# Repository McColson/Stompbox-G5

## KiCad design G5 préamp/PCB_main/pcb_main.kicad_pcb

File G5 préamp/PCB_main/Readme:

Kicad Project files for the main PCB
pcb_main.png

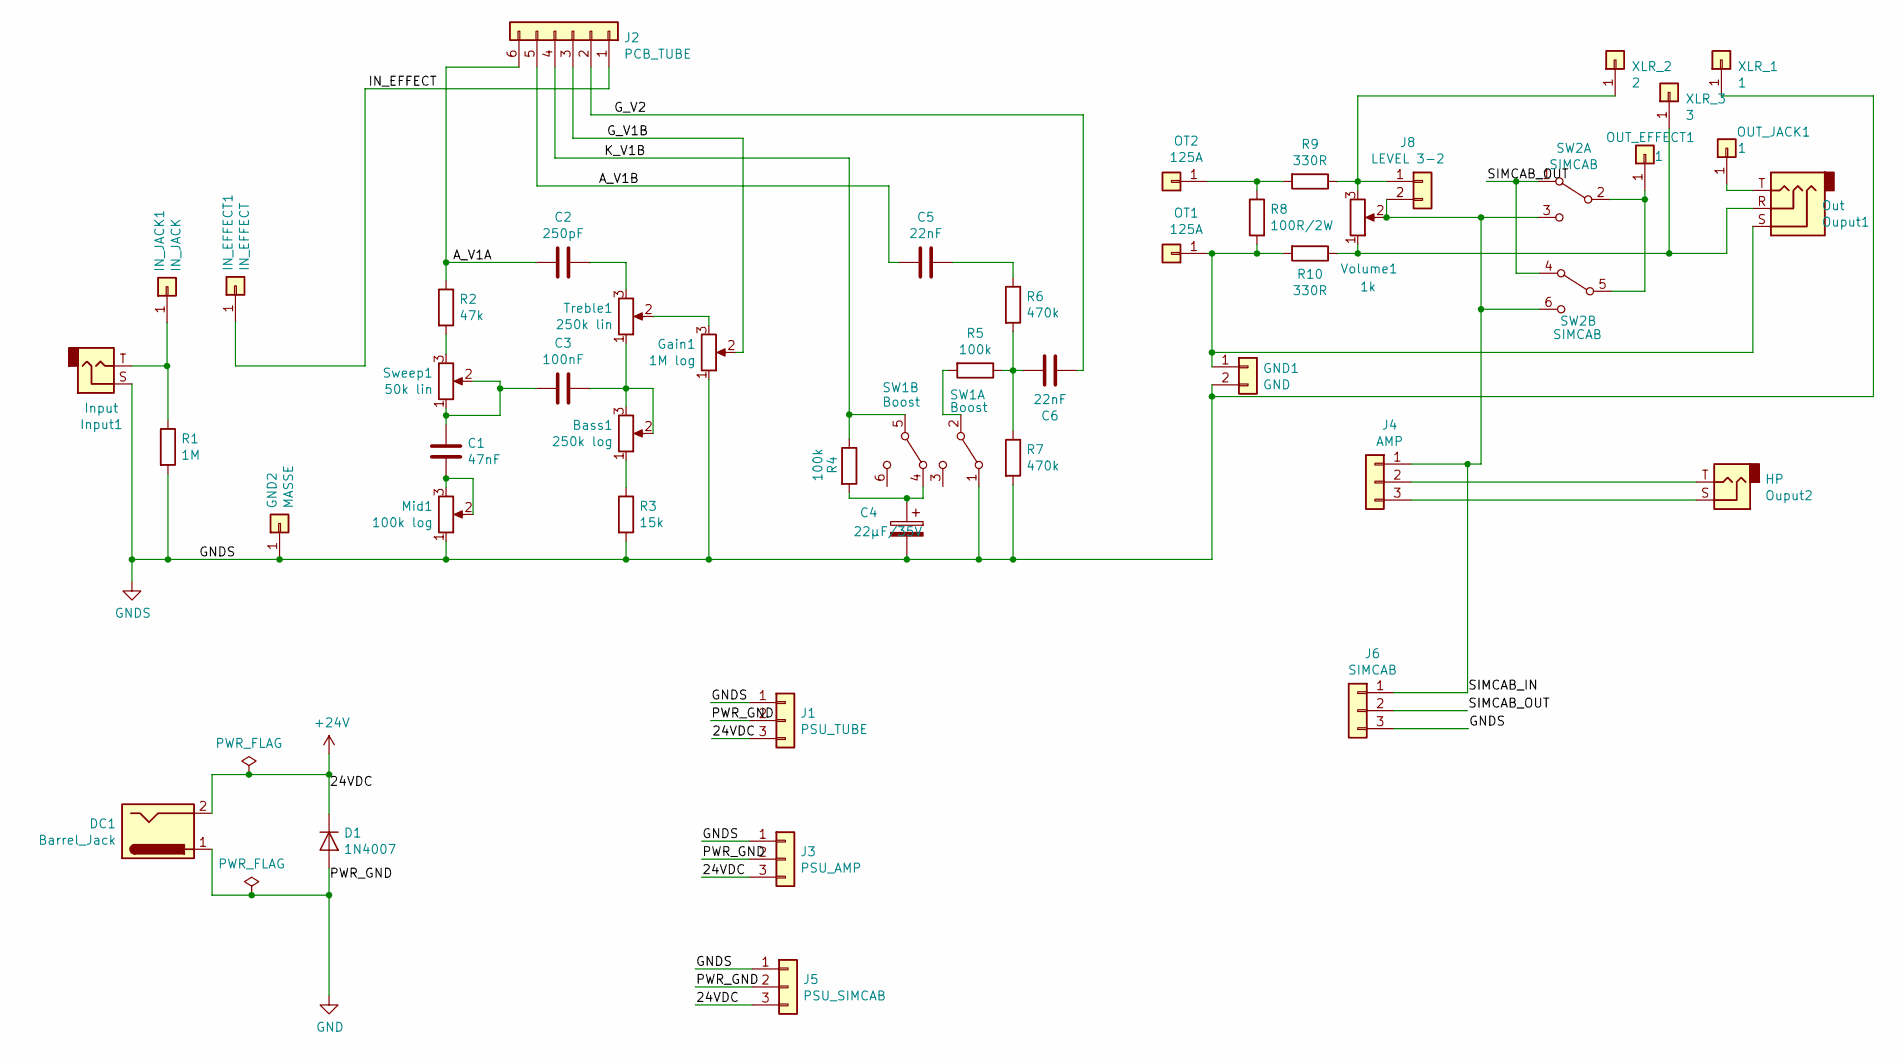
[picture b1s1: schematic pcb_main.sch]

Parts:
Bass1: 250k log; Potentiometer_Omeg_PC16BU_Vertical
C1: 47nF; C_Rect_L7.2mm_W3.0mm_P5.00mm_FKS2_FKP2_MKS2_MKP2
C2: 250pF; C_Disc_D7.5mm_W5.0mm_P7.50mm
C3: 100nF; C_Rect_L7.2mm_W3.0mm_P5.00mm_FKS2_FKP2_MKS2_MKP2
C4: 22µF/35V; CP_Radial_D6.3mm_P2.50mm
C5, C6: 22nF; C_Rect_L7.2mm_W3.0mm_P5.00mm_FKS2_FKP2_MKS2_MKP2
D1: 1N4007; D_DO-41_SOD81_P7.62mm_Horizontal
DC1: Barrel_Jack; BarrelJack_Horizontal
GND1: GND; SolderWirePad_1x02_P7.62mm_Drill2mm
GND2: MASSE; SolderWirePad_1x01_Drill2mm
Gain1: 1M log; Potentiometer_Omeg_PC16BU_Vertical
IN_EFFECT1: IN_EFFECT; SolderWirePad_1x01_Drill2mm
IN_JACK1: IN_JACK; SolderWirePad_1x01_Drill2mm
Input1: Input; Jack_3.5mm_Neutrik_NMJ6HCD2_Horizontal
J1: PSU_TUBE; PinHeader_1x03_P2.54mm_Horizontal
J2: PCB_TUBE; PinHeader_1x06_P2.54mm_Horizontal
J3: PSU_AMP; PinHeader_1x03_P2.54mm_Horizontal
J4: AMP; PinHeader_1x03_P2.54mm_Horizontal
J5: PSU_SIMCAB; PinHeader_1x03_P2.54mm_Horizontal
J6: SIMCAB; PinHeader_1x03_P2.54mm_Horizontal
J8: LEVEL 3-2; SolderJumper-2_P1.3mm_Open_Pad1.0x1.5mm
Mid1: 100k log; Potentiometer_Omeg_PC16BU_Vertical
OT1, OT2: 125A; SolderWirePad_1x01_Drill2mm
OUT_EFFECT1: 1; SolderWirePad_1x01_Drill2mm
OUT_JACK1: 1; SolderWirePad_1x01_Drill2mm
Ouput1: Out; Jack_3.5mm_Neutrik_NMJ6HCD2_Horizontal
Ouput2: HP; Jack_3.5mm_Neutrik_NMJ6HCD2_Horizontal
R1: 1M; R_Axial_DIN0207_L6.3mm_D2.5mm_P7.62mm_Horizontal
R2: 47k; R_Axial_DIN0207_L6.3mm_D2.5mm_P7.62mm_Horizontal
R3: 15k; R_Axial_DIN0207_L6.3mm_D2.5mm_P7.62mm_Horizontal
R4, R5: 100k; R_Axial_DIN0207_L6.3mm_D2.5mm_P7.62mm_Horizontal
R6, R7: 470k; R_Axial_DIN0207_L6.3mm_D2.5mm_P7.62mm_Horizontal
R8: 100R/2W; R_Axial_DIN0207_L6.3mm_D2.5mm_P10.16mm_Horizontal
R9, R10: 330R; R_Axial_DIN0207_L6.3mm_D2.5mm_P7.62mm_Horizontal
SW1: Boost; SW_CK_Lever_DPDT_72xx
SW2: SIMCAB; SW_CK_Lever_DPDT_72xx
Sweep1: 50k lin; Potentiometer_Omeg_PC16BU_Vertical
Treble1: 250k lin; Potentiometer_Omeg_PC16BU_Vertical
Volume1: 1k; Potentiometer_Omeg_PC16BU_Vertical
XLR_1: 1; SolderWirePad_1x01_Drill2mm
XLR_2: 2; SolderWirePad_1x01_Drill2mm
XLR_3: 3; SolderWirePad_1x01_Drill2mm

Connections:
+24V: D1.1 (K), DC1.2, J1.3, J3.3, J5.3
/A_V1A: C2.2, J2.6, R2.1
/A_V1B: C5.2, J2.5
/G_V1B: Gain1.2, J2.3
/G_V2: C6.1, J2.2
/IN_EFFECT: IN_EFFECT1.1, J2.1
/K_V1B: J2.4, R4.1, SW1.5 (B)
/SIMCAB_IN: J4.1, J6.1, J8.2, SW2.3 (C), SW2.6 (C), Volume1.2
/SIMCAB_OUT: J6.2, SW2.1 (A), SW2.4 (A)
GND: D1.2 (A), DC1.1, J1.2, J3.2, J5.2
GNDS: C4.2, GND1.2, GND2.1, Gain1.1, Input1.S, J1.1, J3.1, J5.1, J6.3, Mid1.1, R1.2, R3.2, R7.2, SW1.1 (A), XLR_1.1
unnamed: Bass1.1, R3.1
unnamed: Bass1.2, Bass1.3, C3.1, Treble1.1
unnamed: C1.1, C3.2, Sweep1.1, Sweep1.2
unnamed: C1.2, Mid1.2, Mid1.3
unnamed: C2.1, Treble1.3
unnamed: C4.1, R4.2, SW1.4 (A)
unnamed: C5.1, R6.1
unnamed: C6.2, R5.1, R6.2, R7.1
unnamed: GND1.1, OT1.1, Ouput1.S, R8.2, R10.2
unnamed: Gain1.3, Treble1.2
unnamed: IN_JACK1.1, Input1.T, R1.1
unnamed: J4.2, Ouput2.T
unnamed: J4.3, Ouput2.S
unnamed: J8.1, R9.1, Volume1.3, XLR_2.1
unnamed: OT2.1, R8.1, R9.2
unnamed: OUT_EFFECT1.1, SW2.2 (B), SW2.5 (B)
unnamed: OUT_JACK1.1, Ouput1.T
unnamed: Ouput1.R, R10.1, Volume1.1, XLR_3.1
unnamed: R2.2, Sweep1.3
unnamed: R5.2, SW1.2 (B)

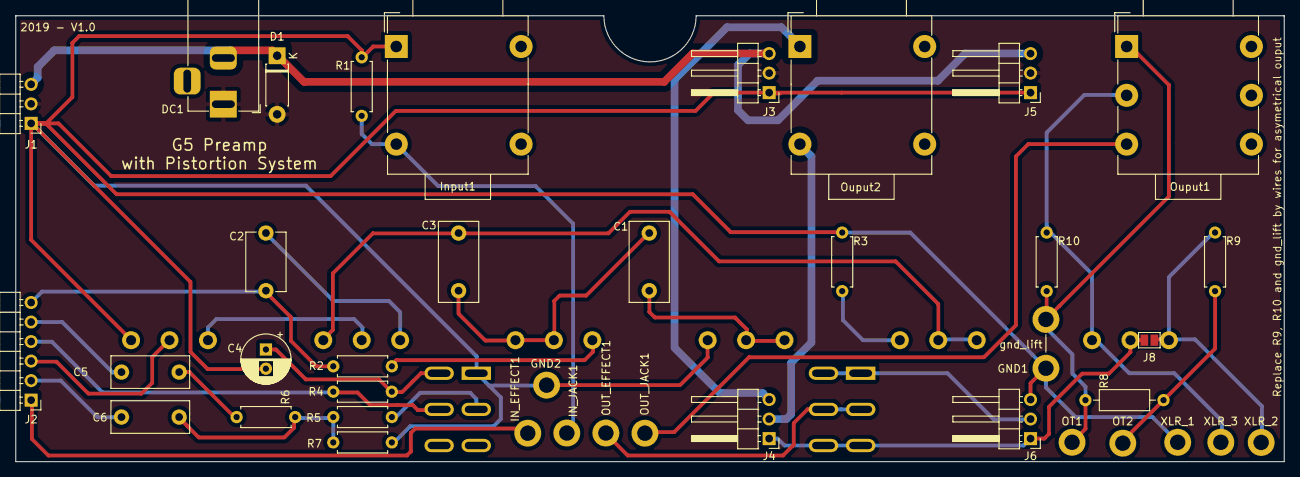
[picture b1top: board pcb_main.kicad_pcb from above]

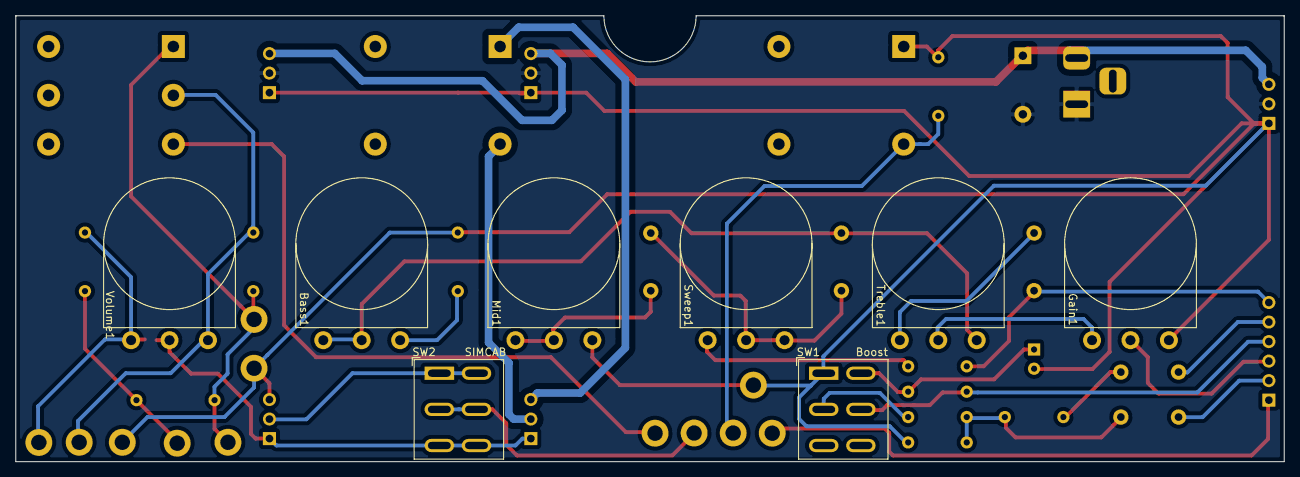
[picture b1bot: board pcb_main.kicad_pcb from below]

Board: 2 copper layers, 165.0 x 58.0 mm, 47 parts (8 on the bottom side), 31 nets.

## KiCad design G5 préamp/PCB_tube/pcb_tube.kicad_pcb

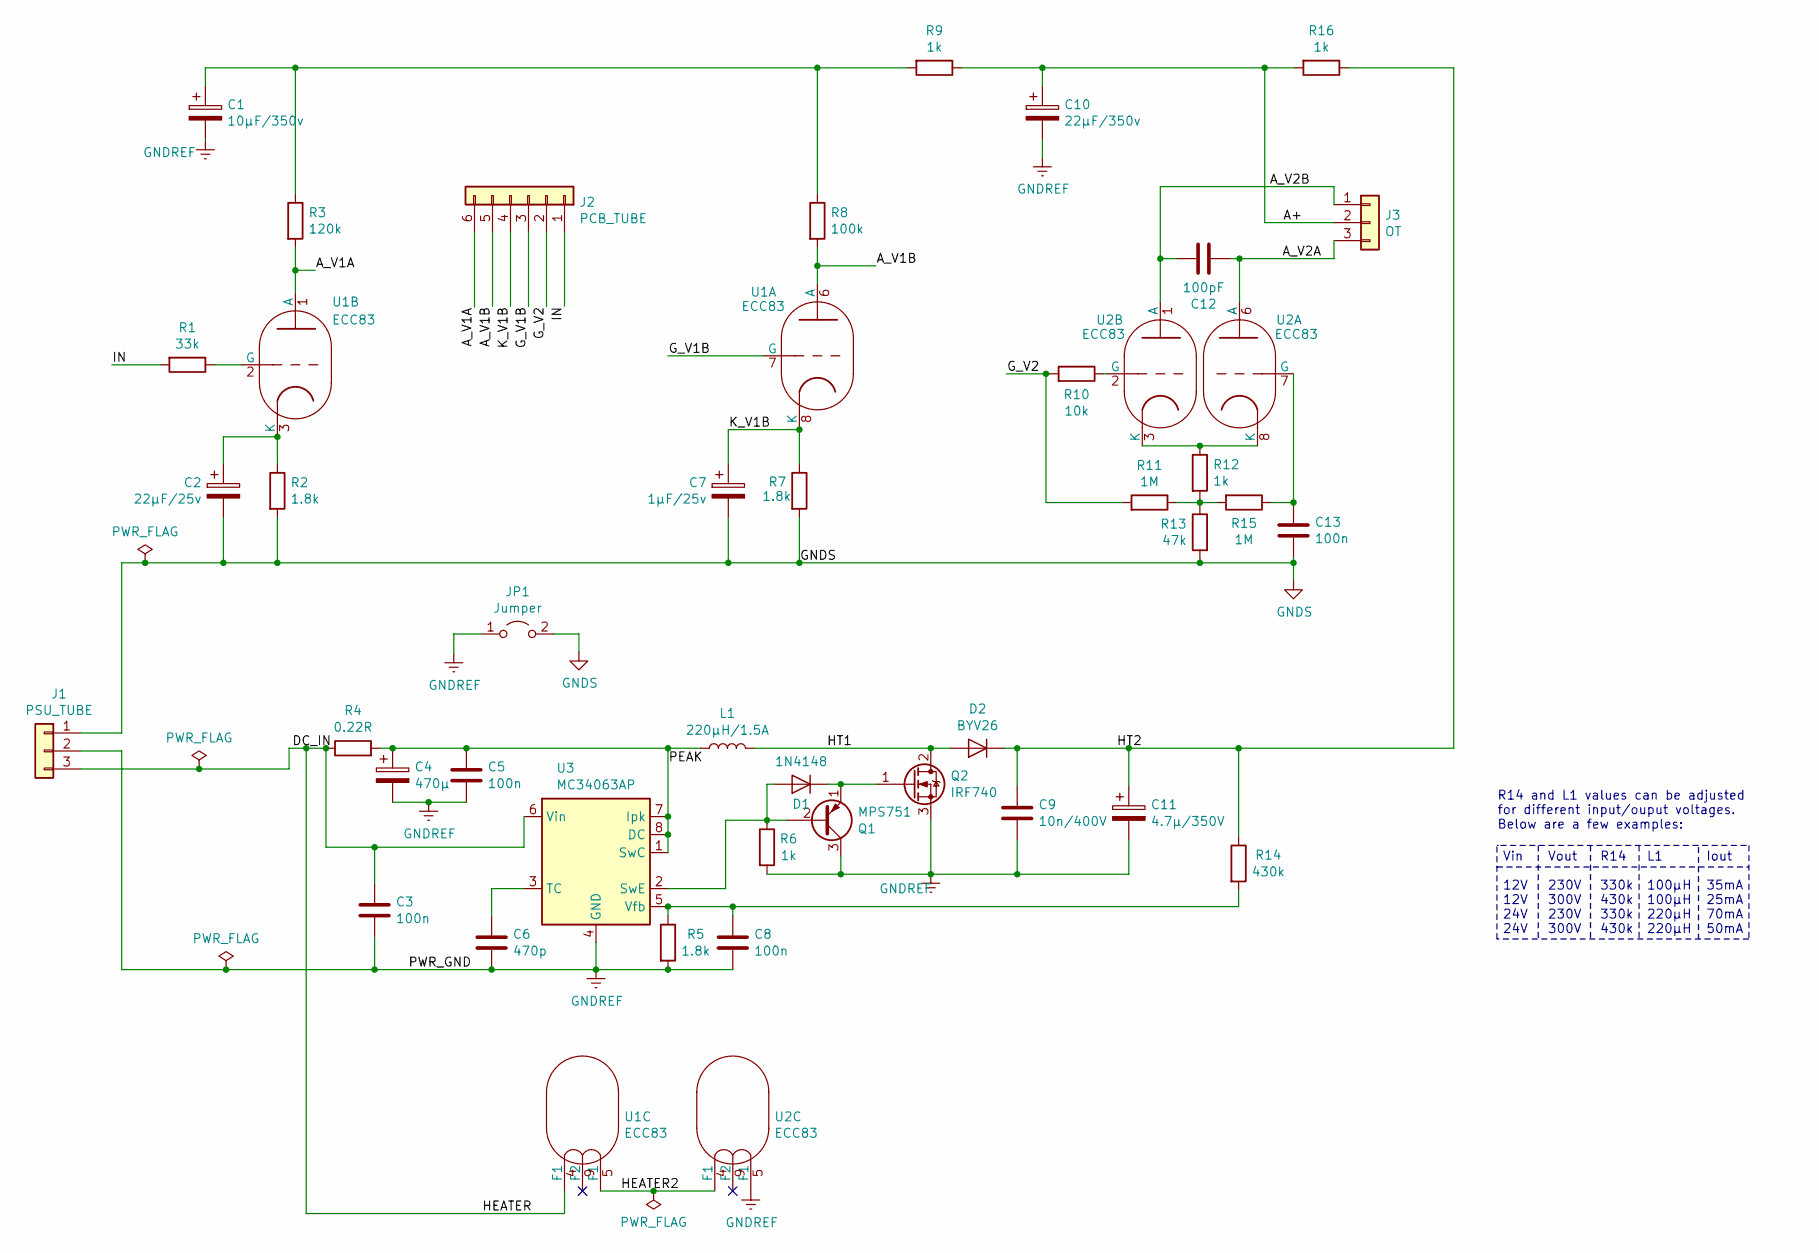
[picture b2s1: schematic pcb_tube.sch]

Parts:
C1: 10µF/350v; CP_Radial_D10.0mm_P5.00mm
C2: 22µF/25v; CP_Radial_D6.3mm_P2.50mm
C3, C5, C8: 100n; C_Rect_L7.2mm_W3.0mm_P5.00mm_FKS2_FKP2_MKS2_MKP2; MPN MKS2D031001A00KI00
C4: 470µ; CP_Radial_D10.0mm_P5.00mm; MPN UVR1V471MPD
C6: 470p; C_Disc_D6.0mm_W4.4mm_P5.00mm; MPN C322C471J2G5TA
C7: 1µF/25v; CP_Radial_D6.3mm_P2.50mm
C9: 10n/400V; C_Disc_D6.0mm_W4.4mm_P5.00mm; MPN C322C103KBR5TA
C10: 22µF/350v; CP_Radial_D13.0mm_P5.00mm
C11: 4.7µ/350V; CP_Radial_D10.0mm_P5.00mm; MPN UBT2V4R7MPD8
C12: 100pF; C_Disc_D7.5mm_W5.0mm_P7.50mm
C13: 100n; C_Rect_L7.2mm_W3.0mm_P5.00mm_FKS2_FKP2_MKS2_MKP2
D1: 1N4148; D_DO-35_SOD27_P7.62mm_Horizontal; MPN 1N4148TR
D2: BYV26; D_DO-15_P10.16mm_Horizontal; MPN BYV26E-TAP
J1: PSU_TUBE; PinSocket_1x03_P2.54mm_Vertical
J2: PCB_TUBE; PinSocket_1x06_P2.54mm_Vertical
J3: OT; TerminalBlock_bornier-3_P5.08mm
JP1: Jumper; SolderJumper-2_P1.3mm_Bridged_RoundedPad1.0x1.5mm
L1: 220µH/1.5A; L_Radial_D10.5mm_P5.00mm_MuRATA_1200RS; MPN 12RS104C
Q1: MPS751; TO-92_Inline_Wide; MPN MPS751G
Q2: IRF740; TO-220-3_Vertical; MPN IRF740LCPBF
R1: 33k; R_Axial_DIN0207_L6.3mm_D2.5mm_P7.62mm_Horizontal
R2, R7: 1.8k; R_Axial_DIN0207_L6.3mm_D2.5mm_P7.62mm_Horizontal
R3: 120k; R_Axial_DIN0207_L6.3mm_D2.5mm_P7.62mm_Horizontal
R4: 0.22R; R_Axial_DIN0207_L6.3mm_D2.5mm_P7.62mm_Horizontal; MPN LR1F220R
R5: 1.8k; R_Axial_DIN0207_L6.3mm_D2.5mm_P7.62mm_Horizontal; MPN LR1F1K8
R6: 1k; R_Axial_DIN0207_L6.3mm_D2.5mm_P7.62mm_Horizontal; MPN LR1F1K0
R8: 100k; R_Axial_DIN0207_L6.3mm_D2.5mm_P7.62mm_Horizontal
R9, R12, R16: 1k; R_Axial_DIN0207_L6.3mm_D2.5mm_P7.62mm_Horizontal
R10: 10k; R_Axial_DIN0207_L6.3mm_D2.5mm_P7.62mm_Horizontal
R11, R15: 1M; R_Axial_DIN0207_L6.3mm_D2.5mm_P7.62mm_Horizontal
R13: 47k; R_Axial_DIN0207_L6.3mm_D2.5mm_P7.62mm_Horizontal
R14: 430k; R_Axial_DIN0207_L6.3mm_D2.5mm_P7.62mm_Horizontal; MPN YR1B432KCC
U1, U2: ECC83; Valve_Noval-B9A_Belton-VT9-PT_Socket
U3: MC34063AP; DIP-8_W7.62mm_LongPads; MPN MC34063AP1G

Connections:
/A+: C10.1, R9.1, R16.2; also elsewhere on the board
/A_V1A: J2.6, R3.2, U1.1 (A)
/A_V1B: J2.5, R8.2, U1.6 (A)
/A_V2A: C12.1, U2.6 (A); also elsewhere on the board
/A_V2B: C12.2, U2.1 (A); also elsewhere on the board
/DC_IN: C3.1, J1.3, R4.1, U1.4 (F1), U3.6 (Vin)
/G_V1B: J2.3, U1.7 (G)
/G_V2: J2.2, R10.2, R11.2
/HEATER2: U1.5 (F1), U2.4 (F1)
/HT1: D2.2 (A), L1.2, Q2.2 (D)
/HT2: C9.1, C11.1, D2.1 (K), R14.1, R16.1
/IN: J2.1, R1.2
/K_V1B: C7.1, J2.4, R7.1, U1.8 (K)
/PEAK: C4.1, C5.1, L1.1, R4.2, U3.1 (SwC), U3.7 (Ipk), U3.8 (DC)
GNDREF: C1.2, C3.2, C4.2, C5.2, C6.2, C8.2, C9.2, C10.2, C11.2, J1.2, JP1.1 (A), Q1.3 (C), Q2.3 (S), R5.2, R6.2, U2.5 (F1), U3.4 (GND)
GNDS: C2.2, C7.2, C13.2, J1.1, JP1.2 (B), R2.2, R7.2, R13.2
unnamed: C1.1, R3.1, R8.1, R9.2
unnamed: C2.1, R2.1, U1.3 (K)
unnamed: C6.1, U3.3 (TC)
unnamed: C8.1, R5.1, R14.2, U3.5 (Vfb)
unnamed: C13.1, R15.1, U2.7 (G)
unnamed: D1.1 (K), Q1.1 (E), Q2.1 (G)
unnamed: D1.2 (A), Q1.2 (B), R6.1, U3.2 (SwE)
unnamed: R1.1, U1.2 (G)
unnamed: R10.1, U2.2 (G)
unnamed: R11.1, R12.2, R13.1, R15.2
unnamed: R12.1, U2.3 (K), U2.8 (K)

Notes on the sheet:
Vin 12V 12V 24V 24V
Vout 230V 300V 230V 300V
R14 330k 430k 330k 430k
L1 100µH 100µH 220µH 220µH
Iout 35mA 25mA 70mA 50mA
R14 and L1 values can be adjusted for different input/ouput voltages. Below are a few examples:

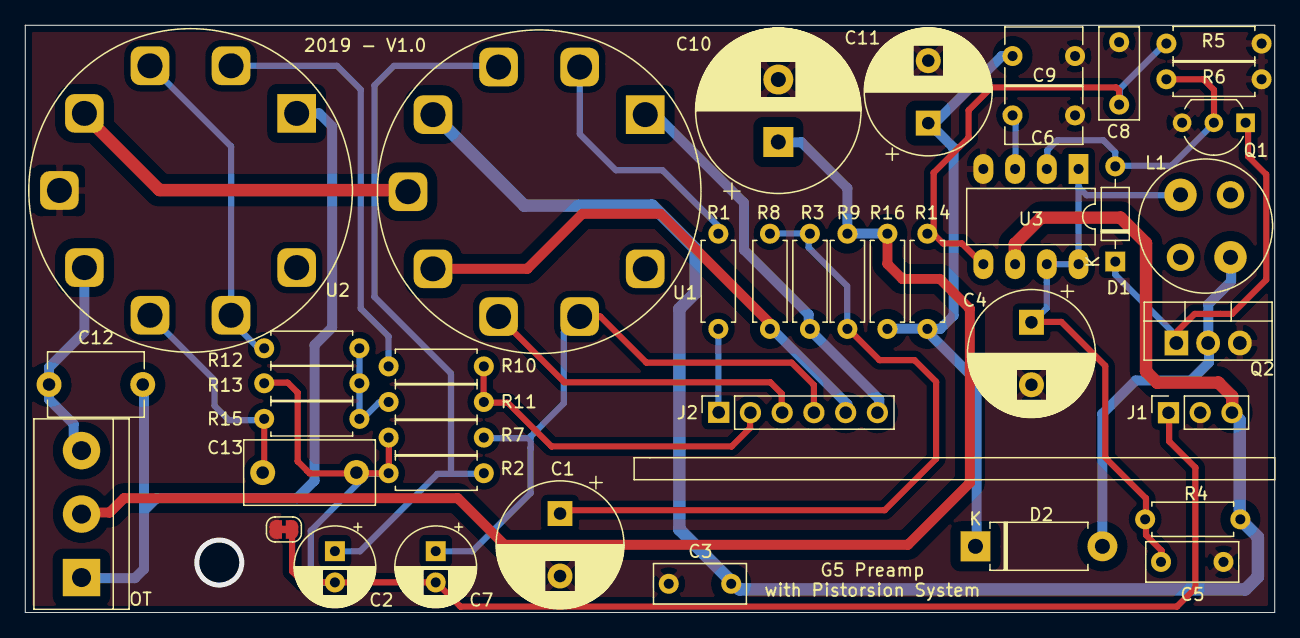
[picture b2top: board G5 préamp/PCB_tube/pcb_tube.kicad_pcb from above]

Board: 2 copper layers, 100.0 x 47.0 mm, 41 parts (0 on the bottom side), 27 nets.

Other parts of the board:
OT: OT; TerminalBlock_bornier-3_P5.08mm

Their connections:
/A+: OT.2; also elsewhere on the board
/A_V2A: OT.3; also elsewhere on the board
/A_V2B: OT.1; also elsewhere on the board

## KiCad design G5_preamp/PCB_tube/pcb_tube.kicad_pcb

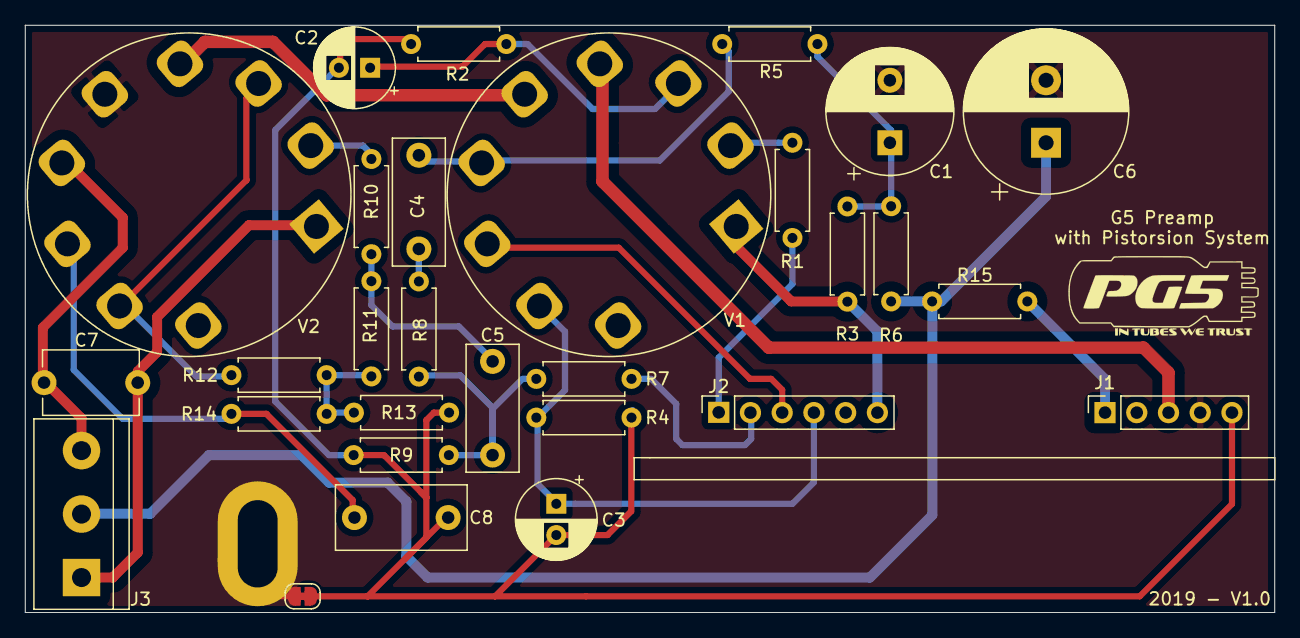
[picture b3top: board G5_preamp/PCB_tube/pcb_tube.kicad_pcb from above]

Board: 2 copper layers, 100.0 x 47.0 mm, 29 parts (0 on the bottom side), 24 nets.

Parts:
C1: 10µF/350v; CP_Radial_D10.0mm_P5.00mm
C2: 22µF/25v; CP_Radial_D6.3mm_P2.50mm
C3: 1µF/25v; CP_Radial_D6.3mm_P2.50mm
C4, C5: 22nF; C_Rect_L10.0mm_W4.0mm_P7.50mm_MKS4
C6: 22µF/350v; CP_Radial_D13.0mm_P5.00mm
C7: 100pF; C_Disc_D7.5mm_W5.0mm_P7.50mm
C8: 100n; C_Rect_L10.3mm_W5.0mm_P7.50mm_MKS4
J1: PSU_TUBE; PinSocket_1x05_P2.54mm_Vertical
J2: PCB_TUBE; PinSocket_1x06_P2.54mm_Vertical
J3: OT; TerminalBlock_bornier-3_P5.08mm
JP1: Jumper; SolderJumper-2_P1.3mm_Bridged_RoundedPad1.0x1.5mm
R1: 33k; R_Axial_DIN0207_L6.3mm_D2.5mm_P7.62mm_Horizontal
R2, R4: 1.8k; R_Axial_DIN0207_L6.3mm_D2.5mm_P7.62mm_Horizontal
R3: 120k; R_Axial_DIN0207_L6.3mm_D2.5mm_P7.62mm_Horizontal
R5, R7: 100k; R_Axial_DIN0207_L6.3mm_D2.5mm_P7.62mm_Horizontal
R6, R12, R15: 1k; R_Axial_DIN0207_L6.3mm_D2.5mm_P7.62mm_Horizontal
R8, R9: 470k; R_Axial_DIN0207_L6.3mm_D2.5mm_P7.62mm_Horizontal
R10: 10k; R_Axial_DIN0207_L6.3mm_D2.5mm_P7.62mm_Horizontal
R11, R14: 1M; R_Axial_DIN0207_L6.3mm_D2.5mm_P7.62mm_Horizontal
R13: 47k; R_Axial_DIN0207_L6.3mm_D2.5mm_P7.62mm_Horizontal
V1, V2: ECC83; Valve_Noval-B9A_Belton-VT9-PT_Socket

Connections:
/24VDC: J1.3, V1.4
/A+: C6.1, J3.2, R6.1, R15.2
/A_V1A: J2.6, R3.2, V1.1
/A_V2A: C7.1, J3.3, V2.6
/A_V2B: C7.2, J3.1, V2.1
/BOOST: J2.2, R7.2
/G_V1B: J2.3, V1.7
/HEATER2: V1.5, V2.4
/HT2: J1.1, R15.1
/IN: J2.1, R1.2
/K_V1B: C3.1, J2.4, R4.1, V1.8
GNDREF: C1.2, C6.2, J1.4, JP1.1, V2.5
GNDS: C2.2, C3.2, C8.2, J1.5, JP1.2, R2.2, R4.2, R9.2, R13.2
unnamed: C1.1, R3.1, R5.1, R6.2
unnamed: C2.1, R2.1, V1.3
unnamed: C4.1, R8.1
unnamed: C4.2, R5.2, V1.6
unnamed: C5.1, R10.2, R11.2
unnamed: C5.2, R7.1, R8.2, R9.1
unnamed: C8.1, R14.1, V2.7
unnamed: R1.1, V1.2
unnamed: R10.1, V2.2
unnamed: R11.1, R12.2, R13.1, R14.2
unnamed: R12.1, V2.3, V2.8
